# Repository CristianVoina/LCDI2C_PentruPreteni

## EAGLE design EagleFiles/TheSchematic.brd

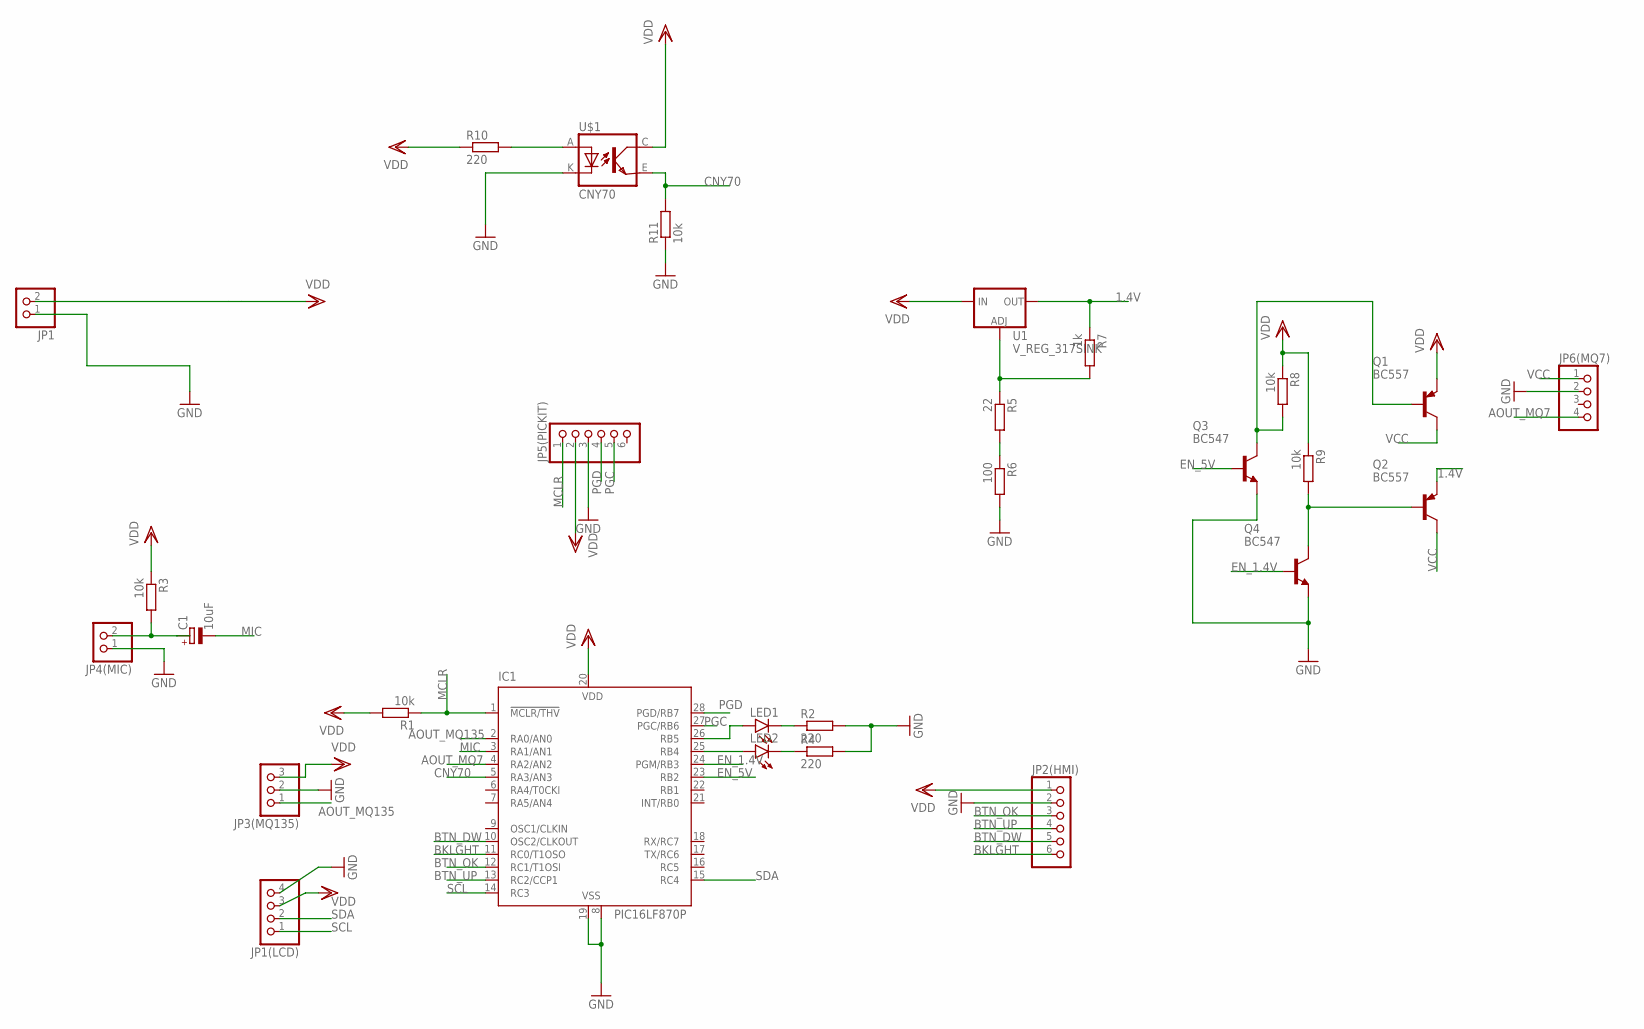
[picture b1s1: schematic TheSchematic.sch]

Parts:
C1: 10uF; E1,8-4
IC1: PIC16LF870P; DIL28-3
JP1, JP4(MIC): PINHD-1X2; 1X02
JP1(LCD), JP6(MQ7): PINHD-1X4; 1X04
JP2(HMI), JP5(PICKIT): PINHD-1X6; 1X06
JP3(MQ135): PINHD-1X3; 1X03
LED1, LED2: LED5MM
Q1, Q2: BC557; TO92-EBC
Q3, Q4: BC547; TO92
R1, R3, R8, R9: 10k; 0204/7
R2, R4, R10: 220; 0207/10
R5: 22; 0204/7
R6: 100; 0204/7
R7: 1k; 0204/7
R11: 10k; 0207/10
U1: V_REG_317SINK; TO220-ADJ
U$1: CNY70; 4

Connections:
1.4V: Q2.E, R7.1, U1.OUT
AOUT_MQ7: IC1.4 (RA2/AN2), JP6(MQ7).4
AOUT_MQ135: IC1.2 (RA0/AN0), JP3(MQ135).1
BKLGHT: IC1.11 (RC0/T1OSO), JP2(HMI).6
BTN_DW: IC1.10 (OSC2/CLKOUT), JP2(HMI).5
BTN_OK: IC1.12 (RC1/T1OSI), JP2(HMI).3
BTN_UP: IC1.13 (RC2/CCP1), JP2(HMI).4
CNY70: IC1.5 (RA3/AN3), R11.2, U$1.E (EMI)
EN_1.4V: IC1.24 (PGM/RB3), Q4.2 (B)
EN_5V: IC1.23 (RB2), Q3.2 (B)
GND: IC1.8 (VSS), IC1.19 (VSS), JP1.1, JP1(LCD).4, JP2(HMI).2, JP3(MQ135).2, JP4(MIC).1, JP5(PICKIT).3, JP6(MQ7).2, Q3.1 (E), Q4.1 (E), R2.2, R4.2, R6.2, R11.1, U$1.K (C)
MCLR: IC1.1 (!MCLR/THV), JP5(PICKIT).1, R1.1
MIC: C1.-, IC1.3 (RA1/AN1)
unnamed: R5.1, R7.2, U1.ADJ
unnamed: IC1.26 (RB5), LED1.A
unnamed: LED1.K (C), R2.1
unnamed: C1.+, JP4(MIC).2, R3.2
unnamed: IC1.25 (RB4), LED2.A
unnamed: LED2.K (C), R4.1
unnamed: R5.2, R6.1
unnamed: R10.2, U$1.A
unnamed: Q1.B, Q3.3 (C), R8.2
unnamed: Q2.B, Q4.3 (C), R9.2
PGC: IC1.27 (PGC/RB6), JP5(PICKIT).5
PGD: IC1.28 (PGD/RB7), JP5(PICKIT).4
SCL: IC1.14 (RC3), JP1(LCD).1
SDA: IC1.15 (RC4), JP1(LCD).2
VCC: JP6(MQ7).1, Q1.C, Q2.C
VDD: IC1.20 (VDD), JP1.2, JP1(LCD).3, JP2(HMI).1, JP3(MQ135).3, JP5(PICKIT).2, Q1.E, R1.2, R3.1, R8.1, R9.1, R10.1, U1.IN, U$1.C (COL)

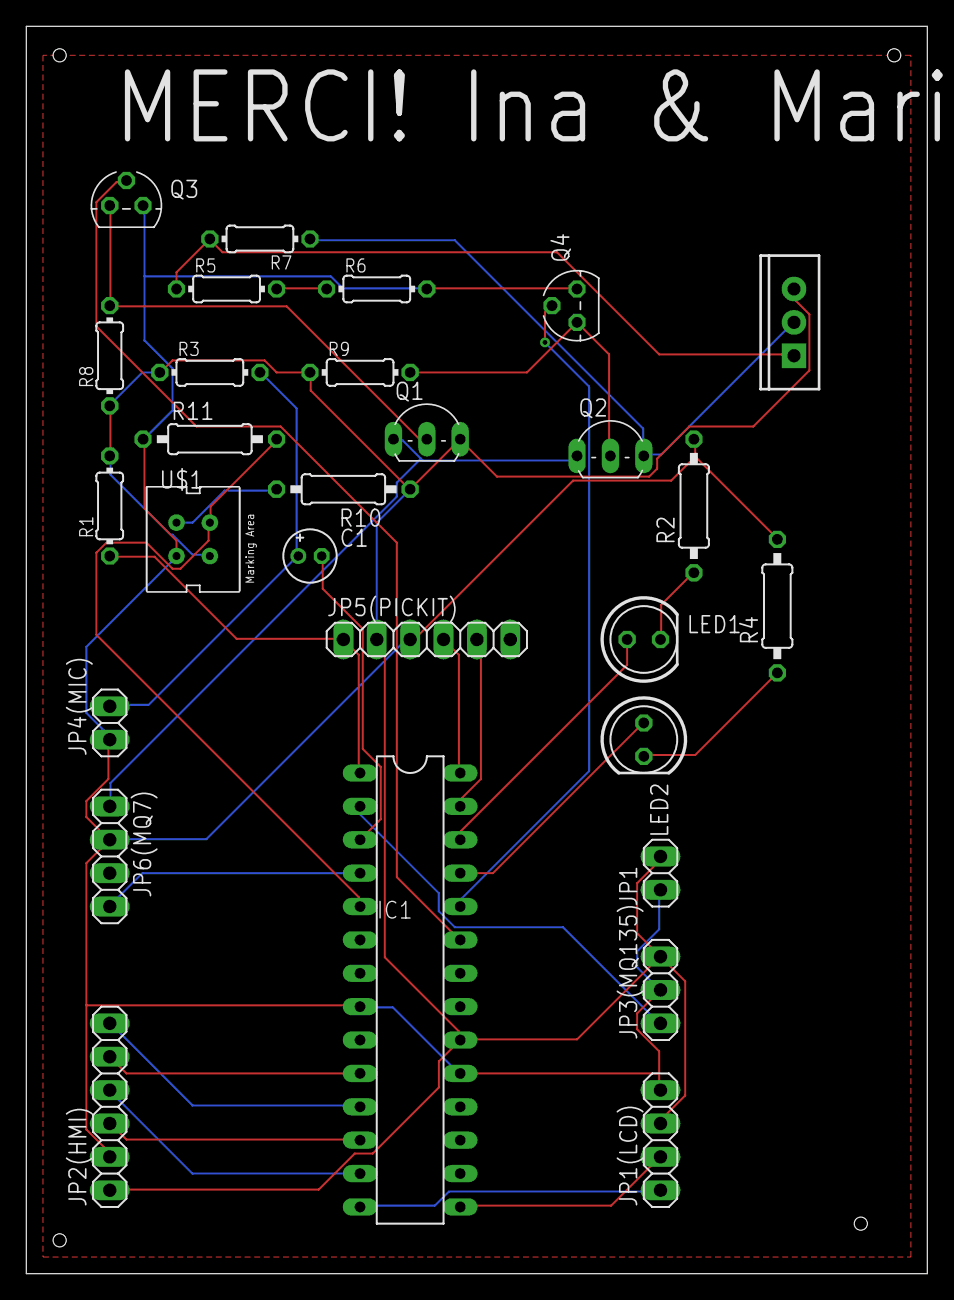
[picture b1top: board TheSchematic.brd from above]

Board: 2 copper layers, 68.6 x 94.9 mm, 28 parts (0 on the bottom side), 29 nets.

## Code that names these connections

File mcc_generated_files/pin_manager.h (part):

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// get/set channel_ANA0 aliases
#define channel_ANA0_TRIS                 TRISAbits.TRISA0
#define channel_ANA0_LAT                  LATAbits.LATA0
#define channel_ANA0_PORT                 PORTAbits.RA0
#define channel_ANA0_WPU                  WPUAbits.WPUA0
#define channel_ANA0_OD                   ODCONAbits.ODCA0
#define channel_ANA0_ANS                  ANSELAbits.ANSA0
#define channel_ANA0_SetHigh()            do { LATAbits.LATA0 = 1; } while(0)
#define channel_ANA0_SetLow()             do { LATAbits.LATA0 = 0; } while(0)
#define channel_ANA0_Toggle()             do { LATAbits.LATA0 = ~LATAbits.LATA0; } while(0)
#define channel_ANA0_GetValue()           PORTAbits.RA0
#define channel_ANA0_SetDigitalInput()    do { TRISAbits.TRISA0 = 1; } while(0)
#define channel_ANA0_SetDigitalOutput()   do { TRISAbits.TRISA0 = 0; } while(0)
#define channel_ANA0_SetPullup()          do { WPUAbits.WPUA0 = 1; } while(0)
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// get/set channel_ANA1 aliases
#define channel_ANA1_TRIS                 TRISAbits.TRISA1
#define channel_ANA1_LAT                  LATAbits.LATA1
#define channel_ANA1_PORT                 PORTAbits.RA1
#define channel_ANA1_WPU                  WPUAbits.WPUA1
#define channel_ANA1_OD                   ODCONAbits.ODCA1
#define channel_ANA1_ANS                  ANSELAbits.ANSA1
#define channel_ANA1_SetHigh()            do { LATAbits.LATA1 = 1; } while(0)
#define channel_ANA1_SetLow()             do { LATAbits.LATA1 = 0; } while(0)
#define channel_ANA1_Toggle()             do { LATAbits.LATA1 = ~LATAbits.LATA1; } while(0)
#define channel_ANA1_GetValue()           PORTAbits.RA1
#define channel_ANA1_SetDigitalInput()    do { TRISAbits.TRISA1 = 1; } while(0)
#define channel_ANA1_SetDigitalOutput()   do { TRISAbits.TRISA1 = 0; } while(0)
#define channel_ANA1_SetPullup()          do { WPUAbits.WPUA1 = 1; } while(0)
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// get/set channel_ANA2 aliases
#define channel_ANA2_TRIS                 TRISAbits.TRISA2
#define channel_ANA2_LAT                  LATAbits.LATA2
#define channel_ANA2_PORT                 PORTAbits.RA2
#define channel_ANA2_WPU                  WPUAbits.WPUA2
#define channel_ANA2_OD                   ODCONAbits.ODCA2
#define channel_ANA2_ANS                  ANSELAbits.ANSA2
#define channel_ANA2_SetHigh()            do { LATAbits.LATA2 = 1; } while(0)
#define channel_ANA2_SetLow()             do { LATAbits.LATA2 = 0; } while(0)
#define channel_ANA2_Toggle()             do { LATAbits.LATA2 = ~LATAbits.LATA2; } while(0)
#define channel_ANA2_GetValue()           PORTAbits.RA2
#define channel_ANA2_SetDigitalInput()    do { TRISAbits.TRISA2 = 1; } while(0)
#define channel_ANA2_SetDigitalOutput()   do { TRISAbits.TRISA2 = 0; } while(0)
#define channel_ANA2_SetPullup()          do { WPUAbits.WPUA2 = 1; } while(0)
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// get/set channel_ANA3 aliases
#define channel_ANA3_TRIS                 TRISAbits.TRISA3
#define channel_ANA3_LAT                  LATAbits.LATA3
#define channel_ANA3_PORT                 PORTAbits.RA3
#define channel_ANA3_WPU                  WPUAbits.WPUA3
#define channel_ANA3_OD                   ODCONAbits.ODCA3
#define channel_ANA3_ANS                  ANSELAbits.ANSA3
#define channel_ANA3_SetHigh()            do { LATAbits.LATA3 = 1; } while(0)
#define channel_ANA3_SetLow()             do { LATAbits.LATA3 = 0; } while(0)
#define channel_ANA3_Toggle()             do { LATAbits.LATA3 = ~LATAbits.LATA3; } while(0)
#define channel_ANA3_GetValue()           PORTAbits.RA3
#define channel_ANA3_SetDigitalInput()    do { TRISAbits.TRISA3 = 1; } while(0)
#define channel_ANA3_SetDigitalOutput()   do { TRISAbits.TRISA3 = 0; } while(0)
#define channel_ANA3_SetPullup()          do { WPUAbits.WPUA3 = 1; } while(0)
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// get/set EN_5V aliases
#define EN_5V_TRIS                 TRISBbits.TRISB2
#define EN_5V_LAT                  LATBbits.LATB2
#define EN_5V_PORT                 PORTBbits.RB2
#define EN_5V_WPU                  WPUBbits.WPUB2
#define EN_5V_OD                   ODCONBbits.ODCB2
#define EN_5V_ANS                  ANSELBbits.ANSB2
#define EN_5V_SetHigh()            do { LATBbits.LATB2 = 1; } while(0)
#define EN_5V_SetLow()             do { LATBbits.LATB2 = 0; } while(0)
#define EN_5V_Toggle()             do { LATBbits.LATB2 = ~LATBbits.LATB2; } while(0)
#define EN_5V_GetValue()           PORTBbits.RB2
#define EN_5V_SetDigitalInput()    do { TRISBbits.TRISB2 = 1; } while(0)
#define EN_5V_SetDigitalOutput()   do { TRISBbits.TRISB2 = 0; } while(0)
#define EN_5V_SetPullup()          do { WPUBbits.WPUB2 = 1; } while(0)
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// get/set EN_14V aliases
#define EN_14V_TRIS                 TRISBbits.TRISB3
#define EN_14V_LAT                  LATBbits.LATB3
#define EN_14V_PORT                 PORTBbits.RB3
#define EN_14V_WPU                  WPUBbits.WPUB3
#define EN_14V_OD                   ODCONBbits.ODCB3
#define EN_14V_ANS                  ANSELBbits.ANSB3
#define EN_14V_SetHigh()            do { LATBbits.LATB3 = 1; } while(0)
#define EN_14V_SetLow()             do { LATBbits.LATB3 = 0; } while(0)
#define EN_14V_Toggle()             do { LATBbits.LATB3 = ~LATBbits.LATB3; } while(0)
#define EN_14V_GetValue()           PORTBbits.RB3
#define EN_14V_SetDigitalInput()    do { TRISBbits.TRISB3 = 1; } while(0)
#define EN_14V_SetDigitalOutput()   do { TRISBbits.TRISB3 = 0; } while(0)
#define EN_14V_SetPullup()          do { WPUBbits.WPUB3 = 1; } while(0)
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// get/set IO_RB4 aliases
#define IO_RB4_TRIS                 TRISBbits.TRISB4
#define IO_RB4_LAT                  LATBbits.LATB4
#define IO_RB4_PORT                 PORTBbits.RB4
#define IO_RB4_WPU                  WPUBbits.WPUB4
#define IO_RB4_OD                   ODCONBbits.ODCB4
#define IO_RB4_ANS                  ANSELBbits.ANSB4
#define IO_RB4_SetHigh()            do { LATBbits.LATB4 = 1; } while(0)
#define IO_RB4_SetLow()             do { LATBbits.LATB4 = 0; } while(0)
#define IO_RB4_Toggle()             do { LATBbits.LATB4 = ~LATBbits.LATB4; } while(0)
#define IO_RB4_GetValue()           PORTBbits.RB4
#define IO_RB4_SetDigitalInput()    do { TRISBbits.TRISB4 = 1; } while(0)
#define IO_RB4_SetDigitalOutput()   do { TRISBbits.TRISB4 = 0; } while(0)
#define IO_RB4_SetPullup()          do { WPUBbits.WPUB4 = 1; } while(0)
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// get/set IO_RB5 aliases
#define IO_RB5_TRIS                 TRISBbits.TRISB5
#define IO_RB5_LAT                  LATBbits.LATB5
#define IO_RB5_PORT                 PORTBbits.RB5
#define IO_RB5_WPU                  WPUBbits.WPUB5
#define IO_RB5_OD                   ODCONBbits.ODCB5
#define IO_RB5_ANS                  ANSELBbits.ANSB5
#define IO_RB5_SetHigh()            do { LATBbits.LATB5 = 1; } while(0)
#define IO_RB5_SetLow()             do { LATBbits.LATB5 = 0; } while(0)
#define IO_RB5_Toggle()             do { LATBbits.LATB5 = ~LATBbits.LATB5; } while(0)
#define IO_RB5_GetValue()           PORTBbits.RB5
#define IO_RB5_SetDigitalInput()    do { TRISBbits.TRISB5 = 1; } while(0)
#define IO_RB5_SetDigitalOutput()   do { TRISBbits.TRISB5 = 0; } while(0)
#define IO_RB5_SetPullup()          do { WPUBbits.WPUB5 = 1; } while(0)
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// get/set BKLGHT aliases
#define BKLGHT_TRIS                 TRISCbits.TRISC0
#define BKLGHT_LAT                  LATCbits.LATC0
#define BKLGHT_PORT                 PORTCbits.RC0
#define BKLGHT_WPU                  WPUCbits.WPUC0
#define BKLGHT_OD                   ODCONCbits.ODCC0
#define BKLGHT_ANS                  ANSELCbits.ANSC0
#define BKLGHT_SetHigh()            do { LATCbits.LATC0 = 1; } while(0)
#define BKLGHT_SetLow()             do { LATCbits.LATC0 = 0; } while(0)
#define BKLGHT_Toggle()             do { LATCbits.LATC0 = ~LATCbits.LATC0; } while(0)
#define BKLGHT_GetValue()           PORTCbits.RC0
#define BKLGHT_SetDigitalInput()    do { TRISCbits.TRISC0 = 1; } while(0)
#define BKLGHT_SetDigitalOutput()   do { TRISCbits.TRISC0 = 0; } while(0)
#define BKLGHT_SetPullup()          do { WPUCbits.WPUC0 = 1; } while(0)
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// get/set SELECT_BTN aliases
#define SELECT_BTN_TRIS                 TRISCbits.TRISC1
#define SELECT_BTN_LAT                  LATCbits.LATC1
#define SELECT_BTN_PORT                 PORTCbits.RC1
#define SELECT_BTN_WPU                  WPUCbits.WPUC1
#define SELECT_BTN_OD                   ODCONCbits.ODCC1
#define SELECT_BTN_ANS                  ANSELCbits.ANSC1
#define SELECT_BTN_SetHigh()            do { LATCbits.LATC1 = 1; } while(0)
#define SELECT_BTN_SetLow()             do { LATCbits.LATC1 = 0; } while(0)
#define SELECT_BTN_Toggle()             do { LATCbits.LATC1 = ~LATCbits.LATC1; } while(0)
#define SELECT_BTN_GetValue()           PORTCbits.RC1
#define SELECT_BTN_SetDigitalInput()    do { TRISCbits.TRISC1 = 1; } while(0)
#define SELECT_BTN_SetDigitalOutput()   do { TRISCbits.TRISC1 = 0; } while(0)
#define SELECT_BTN_SetPullup()          do { WPUCbits.WPUC1 = 1; } while(0)
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// get/set DW_BTN aliases
#define DW_BTN_TRIS                 TRISCbits.TRISC2
#define DW_BTN_LAT                  LATCbits.LATC2
#define DW_BTN_PORT                 PORTCbits.RC2
#define DW_BTN_WPU                  WPUCbits.WPUC2
#define DW_BTN_OD                   ODCONCbits.ODCC2
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
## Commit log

2021-02-09 Initial revision
2021-02-09 Added Schematic Files
2021-02-09 Added Documentation Files

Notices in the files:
mcc_generated_files/pin_manager.h:
(c) 2018 Microchip Technology Inc. and its subsidiaries.
parts and their libraries:
SparkFun-IC-Power: Licensing: Creative Commons ShareAlike 4.0 International - https://creativecommons.org/licenses/by-sa/4.0
